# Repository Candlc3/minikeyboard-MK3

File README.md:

# minikeyboard-MK3
super cool  keyboard with a cool firmware. I will be using this for a future project that ill probably continue next summer. This features 4 keys, which represent arrow keys, and it also has an enter key and an oled displaying everything that is pressed. 

## Features:

Comes with 5 keys,
an oled, 
and some hopes and dreams. 

## CAD Model:
peep this

## PCB OVERVIEW!

yea now peep these! 

and THIS!

##Firmware:

This thingamajig uses QMK firmware, and its powered by the hopes and dreams of 3 chatbots that verified that the code works in the first place. It displays what i type, and when i press enter, it checks if the code i inputted is correct.

##BOM:

Heres everything that should probably make this thing. Its pretty simple.

- 5x 1N4148 DO-35 Diodes.
- 1x 0.91" 128x32 OLED Display
- 1x XIAO RP2040
- 1x Case (3 printed parts)
- 4x Cherry MX Switches
- 4x DSA Keycaps
- 4x M3x16mm screws
- i assume im not missing anything else.

uhhhhhhh
uhhhh

uhhhh fun fact this thing took me two computers to make (the first one's motherboard melted so i had to get a new one after allstate basically returned nothing but a 512gb ssd)

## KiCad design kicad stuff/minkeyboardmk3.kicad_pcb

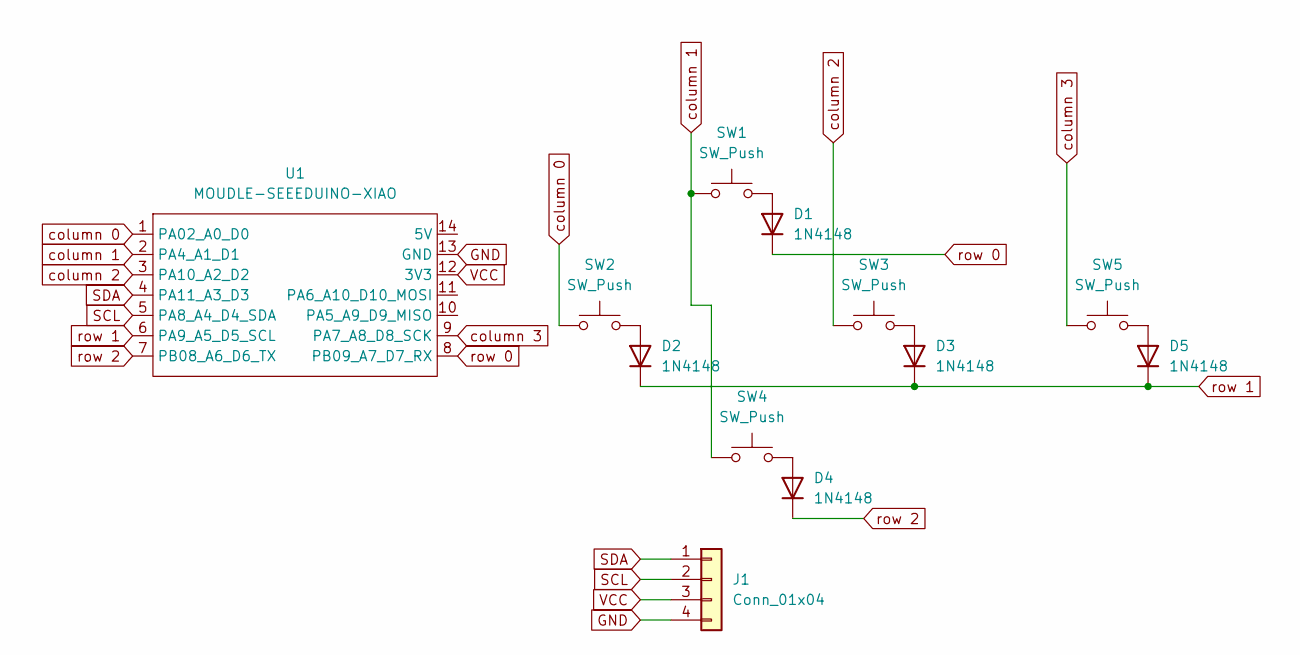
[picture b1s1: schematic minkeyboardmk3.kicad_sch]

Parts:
D1, D2, D3, D4, D5: 1N4148; D_DO-35_SOD27_P7.62mm_Horizontal
J1: Conn_01x04; PinHeader_1x04_P2.54mm_Vertical
SW1, SW2, SW3, SW4, SW5: SW_Push; SW_Cherry_MX_1.00u_PCB
U1: MOUDLE-SEEEDUINO-XIAO; XIAO-Generic-Hybrid-14P-2.54-21X17.8MM

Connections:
GND: J1.4, U1.13 (GND)
unnamed: D1.2 (A), SW1.2
unnamed: D2.2 (A), SW2.2
unnamed: D3.2 (A), SW3.2
unnamed: D4.2 (A), SW4.2
unnamed: D5.2 (A), SW5.2
SCL: J1.2, U1.5 (PA8_A4_D4_SDA)
SDA: J1.1, U1.4 (PA11_A3_D3)
VCC: J1.3, U1.12 (3V3)
column 0: SW2.1, U1.1 (PA02_A0_D0)
column 1: SW1.1, SW4.1, U1.2 (PA4_A1_D1)
column 2: SW3.1, U1.3 (PA10_A2_D2)
column 3: SW5.1, U1.9 (PA7_A8_D8_SCK)
row 0: D1.1 (K), U1.8 (PB09_A7_D7_RX)
row 1: D2.1 (K), D3.1 (K), D5.1 (K), U1.6 (PA9_A5_D5_SCL)
row 2: D4.1 (K), U1.7 (PB08_A6_D6_TX)

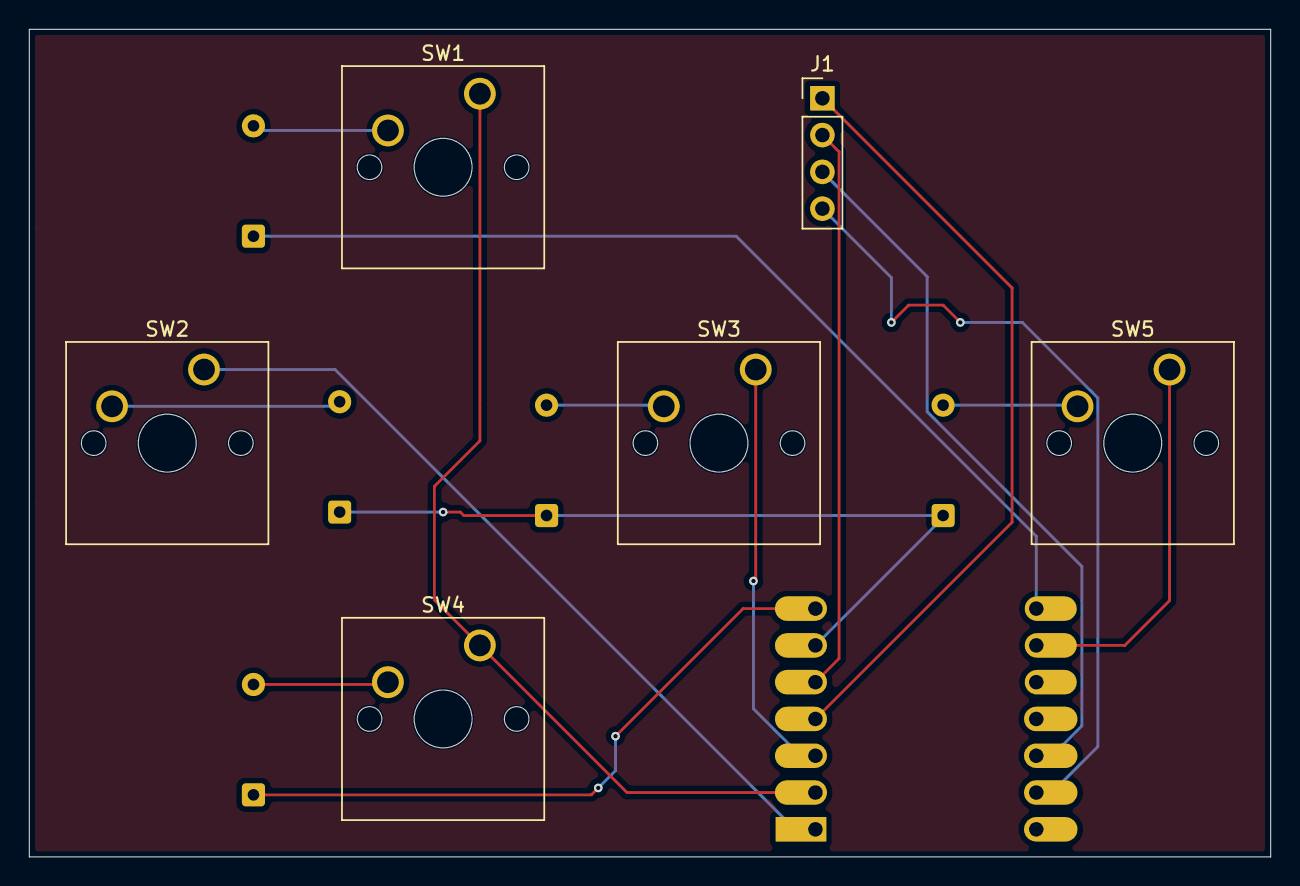
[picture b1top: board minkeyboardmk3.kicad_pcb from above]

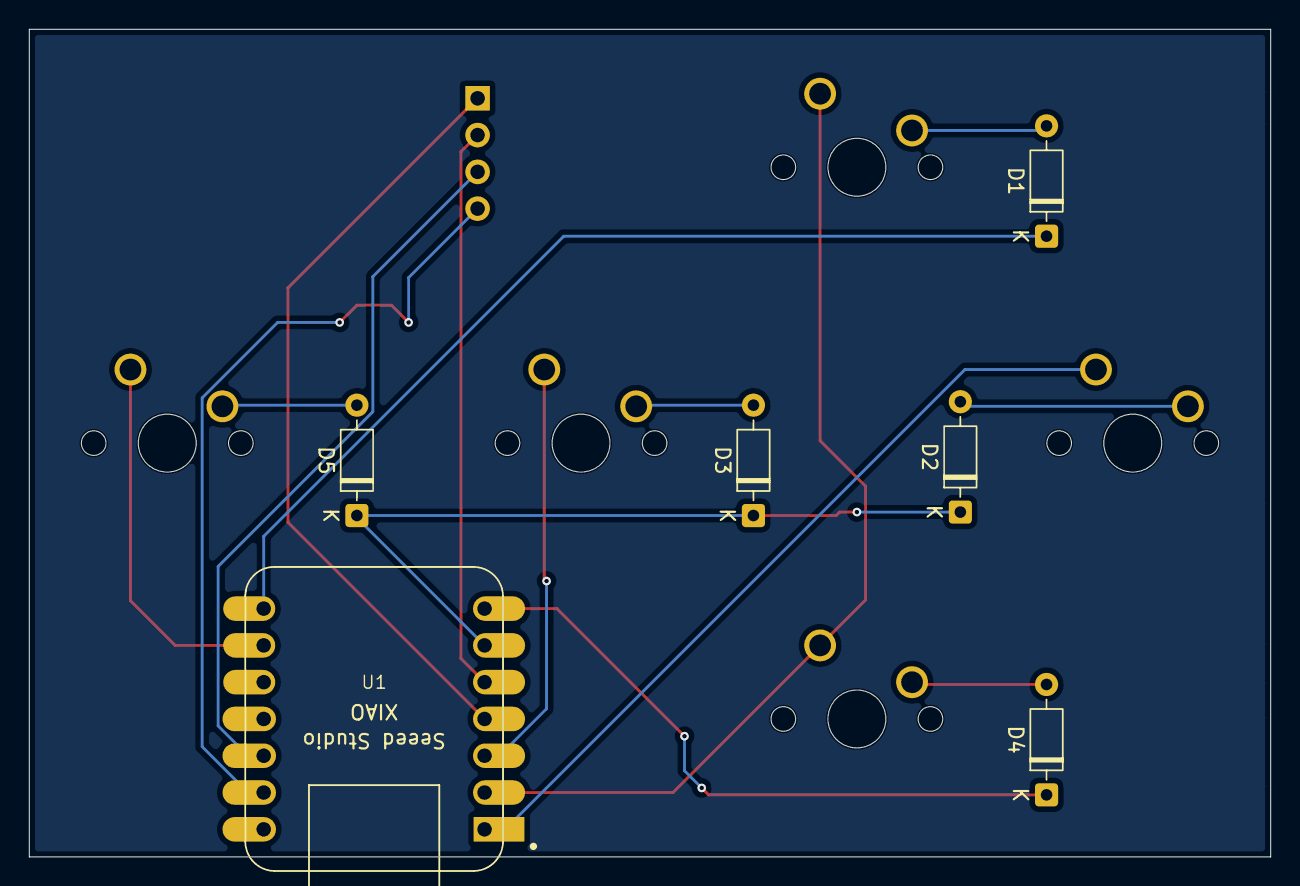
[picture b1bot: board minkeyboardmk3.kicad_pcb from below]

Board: 2 copper layers, 85.7 x 57.2 mm, 12 parts (6 on the bottom side), 16 nets.
